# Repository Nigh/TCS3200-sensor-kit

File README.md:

# TCS3200 Sensor Kit

TCS3200 Sensor Kit 使用 TCS3200 传感器和 RP2040-Zero 采集屏幕光信号，在 Linux 上位机中查看 R/G/B/Clear 四通道波形、建立传感器读数与屏幕 RGB 值的映射，并测试颜色变化后的延迟点击。仓库包含固件、上位机、外壳 3D 设计和 PCB 设计。

## 软件与实测

### 上位机界面

上位机提供波形测量、自动触发测试和颜色校准。波形保留最近 10 秒，支持缩放、暂停快照，以及像素时间桶的 Max/Min/中位数统计。

> **特别说明：** 软件中的颜色校准功能仅用于建立传感器读数与屏幕 RGB 值的映射，不能用于校准屏幕本身的颜色。

### 屏幕采样实拍

实拍条件：屏幕刷新率 **200 Hz**，采样率 **1633 Hz**，采样页面为 UFO Test。

| 数值波形 | 频谱（FFT） |
| --- | --- |
|  |  |

数值波形与频谱截图对应上方实拍中的采样。

### LED 阶跃响应

使用 GP28 驱动白色 LED，记录 TCS3200 亮暗阶跃响应。[测量方法、三组数据、诊断固件编译及测试步骤](firmware/README.md#gp28-led-阶跃响应诊断)见固件说明。

## 外壳与 PCB

### 外壳 3D 设计

使用 Blender 打开 [TCS3200-3D.blend](3D/TCS3200-3D.blend) 编辑外壳。文件说明见 [3D 目录](3D/README.md)。

### PCB 设计

使用 KiCad 打开 [TCS3200-TB.kicad_pro](layout/TCS3200-TB.kicad_pro) 查看原理图与 PCB。文件说明见 [layout 目录](layout/README.md)。

## 快速开始

### 编译与刷写固件

按 [固件接线说明](firmware/README.md#接线) 连接传感器。关闭模块照明 LED，固定传感器与屏幕的距离和角度，并遮挡环境光。RP2040 GPIO 使用 3.3 V 电平；若模块以 5 V 供电，OUT 必须经过电平转换。

在仓库根目录运行：

```sh
make       # 使用 xianii/pico-sdk:2.3.0 Docker 镜像编译
make test  # 主机 C 自检（ASan/UBSan）及 PIO 时序模拟；需要 cc 和 Python 3
```

输出：`firmware/build/src/tcs3200_sensor.uf2`。按住 BOOT 接入 USB，复制 UF2 到引导盘。详细接线与验证见 [固件说明](firmware/README.md)，上位机开发以 [协议 v4](docs/protocol.md) 为准。

### 启动 Linux 上位机

```sh
make host          # 实际设备界面；手动枚举、选择、连接
make host-demo     # 无硬件合成信号演示
make host-build    # host/build/tcs3200-host
make host-test     # 上位机测试和 vet
```

需要 Go 1.27.3+、GTK 3 与 OpenGL。连接设备后点击“枚举设备”，选择端口并连接。没有硬件时可先运行演示模式。串口权限、图表操作、自动触发与颜色映射步骤见 [上位机说明](host/README.md)。

## 采样与触发

固件通过 PIO 测量传感器输出周期，经 USB CDC bulk 传输原始频率；上位机按 50% 占空比换算为脉宽（μs）。RGB+C 可独立开关，低频阈值范围为 100～600000 Hz。启用通道数和低频阈值共同决定最大计划组频率，非空采集为 6～4000 Hz，全关为 0。默认四通道、15 kHz 阈值对应最大 814 Hz。

各通道按顺序采集，并非同时测量。低频或超时通道置零并标记 LOW；屏幕 PWM、刷新和通道间时间偏移会影响颜色判定。

自动触发测试先采集 ARM 参考色，偏离后由 MCU 计时并发送 HID 动作。上位机支持单次或连续左键测试，固件协议还支持键盘和鼠标按钮配置。LOW 无法区分黑屏与传感器断线；USB 轮询和系统调度会增加最终动作延迟，使用前需按实际屏幕和安装条件校准。

## 目录与开发

| 目录 | 内容 |
|---|---|
| [firmware/](firmware/README.md) | Pico SDK + TinyUSB 固件、PIO、接线与上板验证 |
| [host/](host/README.md) | MyGo 原生 Linux 上位机、图表、触发测试与颜色校准 |
| [3D/](3D/README.md) | Blender 外壳设计源文件与预览 |
| [layout/](layout/README.md) | KiCad 工程、原理图、PCB 与预览 |
| [docs/](docs/README.md) | USB 协议与界面、实测图片 |

固件与上位机使用 [USB 二进制协议 v4](docs/protocol.md)，须配套升级。修改协议字段、单位或行为时，同步更新两端实现、协议文档与测试。

## 来源与许可

项目基于 [Nigh/pico-cdc-hid-template](https://github.com/Nigh/pico-cdc-hid-template) 建立，保留 [MIT 许可](LICENSE)。HID 提供键盘和鼠标功能，CDC 用于二进制采样与控制。

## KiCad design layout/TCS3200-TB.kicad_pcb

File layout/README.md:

# PCB 设计

本目录提供 TCS3200 Sensor Kit 的 KiCad 工程、原理图和 PCB 布局。设计文件由 KiCad 10.0 生成。

## 文件

- [TCS3200-TB.kicad_pro](TCS3200-TB.kicad_pro)：KiCad 工程入口。
- [TCS3200-TB.kicad_sch](TCS3200-TB.kicad_sch)：原理图。
- [TCS3200-TB.kicad_pcb](TCS3200-TB.kicad_pcb)：PCB 布局。
- [PCB.jpg](PCB.jpg)：PCB 预览图。

## 使用与修改

使用 KiCad 10.0 或支持该文件格式的版本打开 `.kicad_pro`，进入原理图或 PCB 编辑器。制板前运行电气规则检查（ERC）和设计规则检查（DRC），核对封装、板框、连接与制造要求，再导出生产文件。

连接定义见 [固件接线说明](../firmware/README.md#接线)。修改 GPIO 分配时，同步更新 `firmware/src/sensor.h` 和接线表；调整板形或接口位置时，核对 [外壳设计](../3D/README.md)。

RP2040 GPIO 使用 3.3 V 电平。若传感器模块需要 5 V 供电，OUT 必须经过电平转换，不能直接接入 GPIO；模块照明 LED 保持关闭。

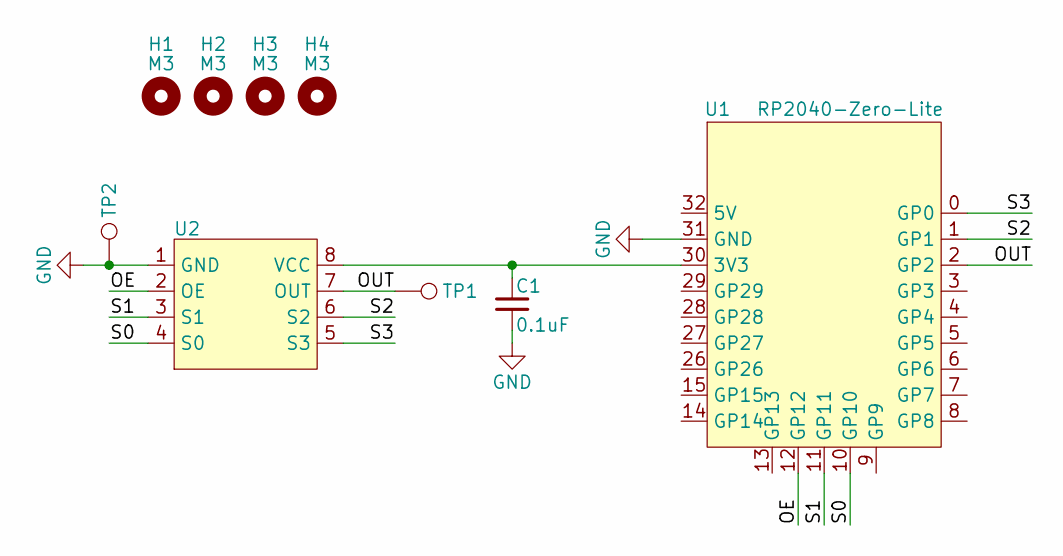
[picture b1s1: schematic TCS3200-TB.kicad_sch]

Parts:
C1: 0.1uF; C_0402_1005Metric_Pad0.74x0.62mm_HandSolder
H1, H2, H3, H4: M3; MountingHole_3.2mm_M3_DIN965_Pad
TP1, TP2: TestPoint; TestPoint_Loop_D1.80mm_Drill1.0mm_Beaded
U1: RP2040-Zero-Lite; RP2040-Zero-Lite-THT
U2: TCS3200-Module-THT

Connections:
/OE: U1.12 (GP12), U2.2 (OE)
/OUT: TP1.1 (1_1), U1.2 (GP2), U2.7 (OUT)
/S0: U1.10 (GP10), U2.4 (S0)
/S1: U1.11 (GP11), U2.3 (S1)
/S2: U1.1 (GP1), U2.6 (S2)
/S3: U1.0 (GP0), U2.5 (S3)
GND: C1.2, TP2.1 (1_1), U1.31 (GND), U2.1 (GND)
unnamed: C1.1, U1.30 (3V3), U2.8 (VCC)

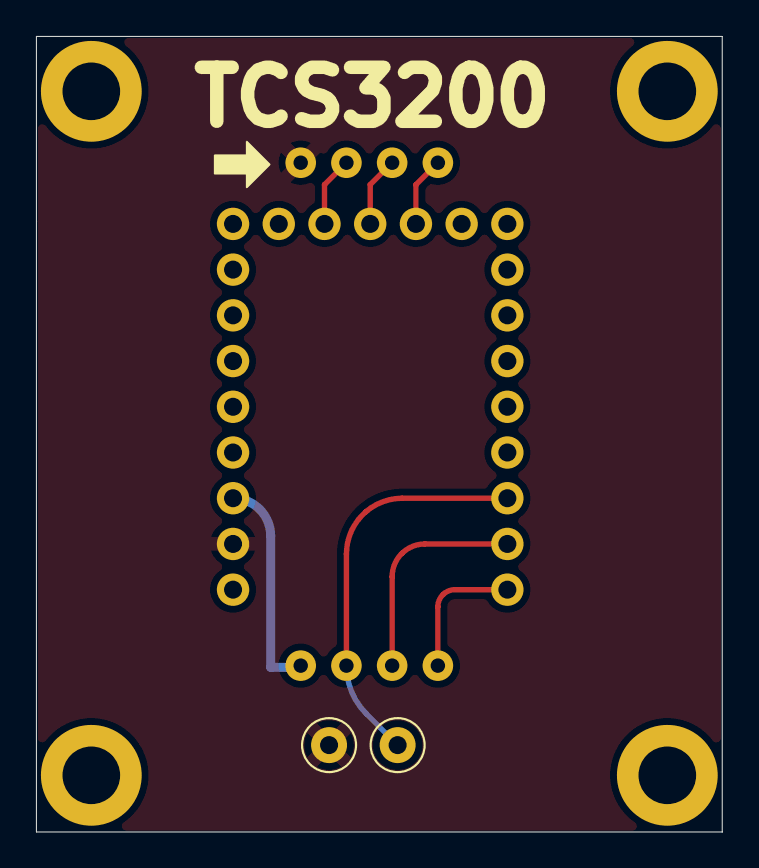
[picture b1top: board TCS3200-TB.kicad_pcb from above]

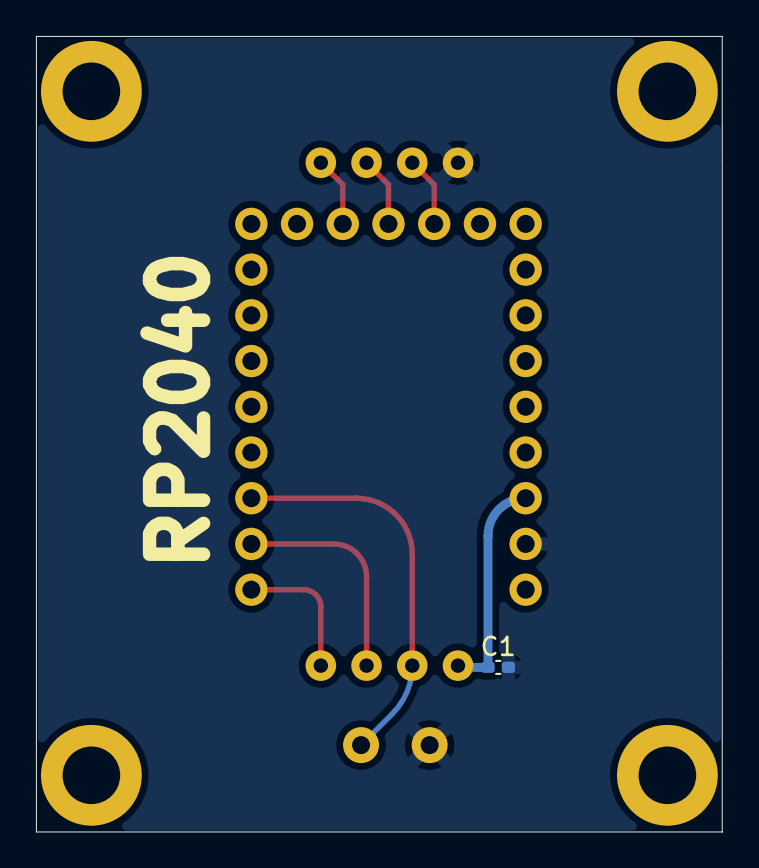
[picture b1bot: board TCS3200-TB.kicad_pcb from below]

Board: 2 copper layers, 38.1 x 44.2 mm, 9 parts (2 on the bottom side), 8 nets.
